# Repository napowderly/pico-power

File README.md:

# pico-power

Wooohooo a new package!

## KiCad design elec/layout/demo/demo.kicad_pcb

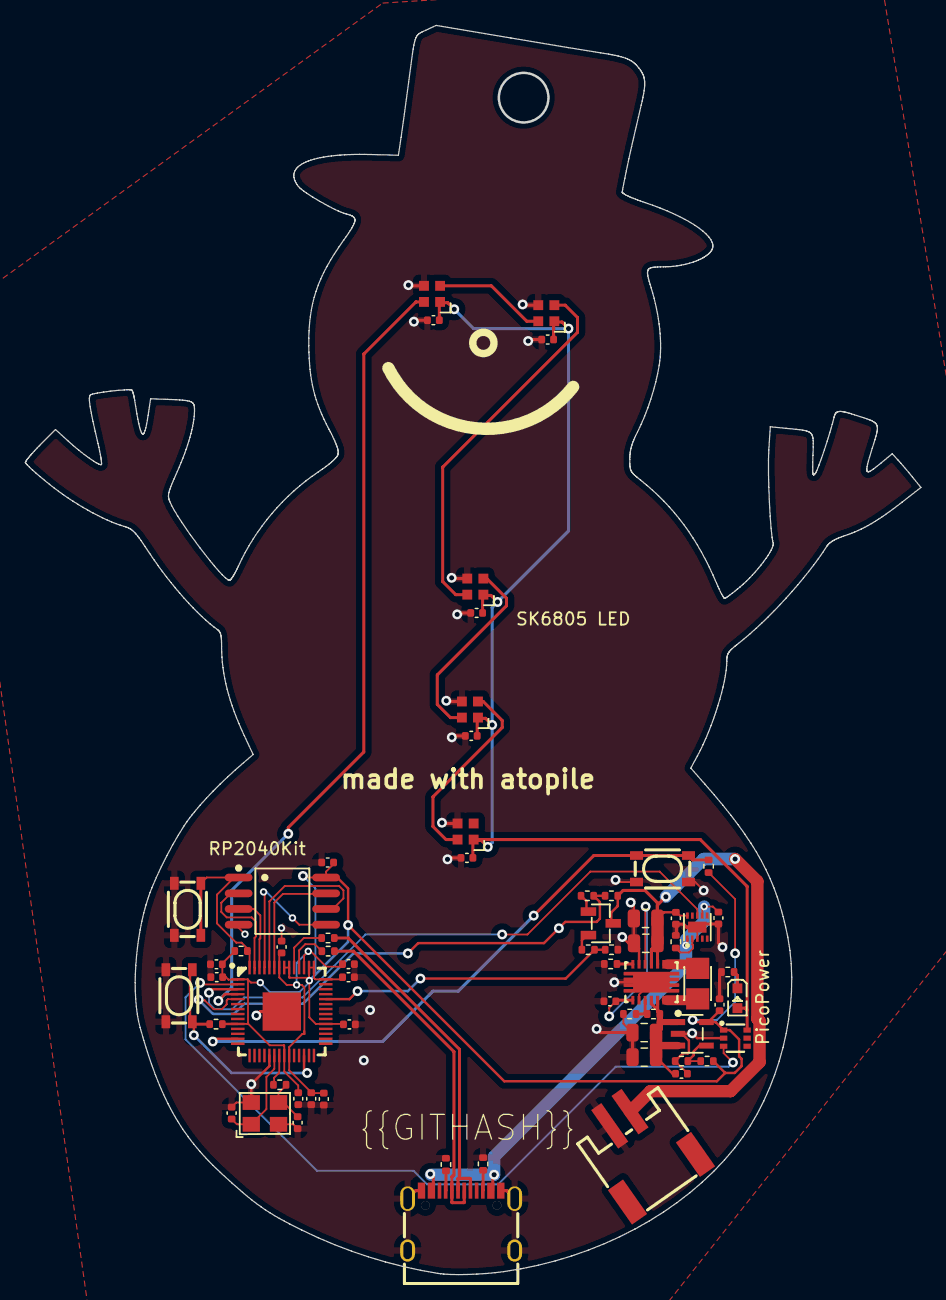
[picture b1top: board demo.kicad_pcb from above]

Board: 2 copper layers, 72.3 x 100.8 mm, 65 parts (0 on the bottom side), 43 nets.

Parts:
C1, C2, C3, C4: 25V 10uF X5R ±10% 0805 Multilayer Ceramic Capacit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; C0805
C5, C12, C13, C14, C15, C16, C18, C19, C20, C22, C23, C24, C25, C26: 16V 100nF X7R ±10% 0402 Multilayer Ceramic Capaci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; C0402
C6, C7, C8, C9, C17, C21: 25V 1uF X5R ±10% 0402 Multilayer Ceramic Capacito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; C0402
C10, C11: 50V 18pF C0G ±5% 0402 Multilayer Ceramic Capacito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; C0402
L1: IND-SMD_L2.5-W2.0_WPN252012H
LED1: LED0603-RD
Q1: SOT-23-3_L2.9-W1.3-P1.90-LS2.4-BR
R1: 62.5mW Thick Film Resistors 50V ±100ppm/℃ ±1% 107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; R0402
R2: 62.5mW Thick Film Resistors 50V ±100ppm/℃ ±5% 360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; R0402
R3: 62.5mW Thick Film Resistors 50V ±100ppm/℃ ±1% 100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; R0402
R4: 62.5mW Thick Film Resistors 50V ±1% ±200ppm/℃ 100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; R0402
R5: 62.5mW Thick Film Resistors 50V ±100ppm/℃ ±1% 24.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; R0402
R6: 62.5mW Thick Film Resistors 50V ±100ppm/℃ ±1% 4.0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; R0402
R7: 62.5mW Thick Film Resistors 50V ±100ppm/℃ ±1% 1MΩ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; R0402
R8: 62.5mW Thick Film Resistors ±100ppm/℃ ±1% 17.4kΩ 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; R0402
R9: 62.5mW Thick Film Resistors 50V ±100ppm/℃ ±1% 10.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; R0402
R10: 62.5mW Thick Film Resistors 75V ±1% ±100ppm/℃ 576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; R0402
R11, R12, R16: 62.5mW Thick Film Resistors 50V ±100ppm/℃ ±1% 10k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; R0402
R13: 62.5mW Thick Film Resistors 50V ±100ppm/℃ ±1% 1kΩ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; R0402
R14, R15: 62.5mW Thick Film Resistors 50V ±100ppm/℃ ±1% 27Ω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; R0402
R17, R18: 62.5mW Thick Film Resistors 50V ±100ppm/℃ ±1% 4.7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; R0402
R19: 62.5mW Thin Film Resistor 50V ±50ppm/℃ ±1% 309Ω 0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; R0402
U1: CONN-SMD_P2.00_S2B-PH-SM4-TB-LF-SN
U2: VSON-14_L4.0-W3.0-P0.50-BL-EP_TI_DSJ
U3: SOT-23-5_L3.0-W1.7-P0.95-LS2.8-BL
U4: SC-70-6_L2.2-W1.3-P0.65-LS2.1-BR
U5: WSON-10_L2.0-W2.0-P0.40-BL-EP
U6: LQFN-56_L7.0-W7.0-P0.4-EP
U7, U8, U11: KEY-SMD_4P-L4.2-W3.2-P2.20-LS4.6
U9: OSC-SMD_4P-L3.2-W2.5-BL
U10: SOIC-8_L5.3-W5.3-P1.27-LS8.0-BL
U12: USB-C-SMD_KH-TYPE-C-16P
U13, U14, U15, U16, U17: LED-SMD_4P-L2.0-W2.0-BR

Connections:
cathode: LED1.1, R19.1
cc1: R17.1, U12.A5
cc2: R18.1, U12.B5
dm: R15.1, U12.A7, U12.B7
dp: R14.2, U12.A6, U12.B6
io0: U6.53, U10.5
io1: U6.55, U10.2
io2: U6.54, U10.3
io3: U6.51, U10.7
iset: R10.1, U5.2
l1: L1.1, U2.8, U2.9
l2: L1.2, U2.6, U2.7
led1.ic-vcc: U13.2, U14.4
led2.ic-vcc: U14.2, U15.4
led3.ic-vcc: U15.2, U16.4
led4.ic-vcc: U16.2, U17.4
micro-cs-1: R12.2, U6.56, U8.1, U8.2, U10.1
micro-sck: R16.2, U6.13, U11.1, U11.2
micro-sck-1: U6.52, U10.6
micro.micro-vcc: C18.1, C19.1, C20.1, C21.1, U6.23, U6.45, U6.50
micro.micro-vcc-1: U6.4, U13.4
micro.osc.osc-out: C11.1, R13.2, U9.3
psu-gnd: C1.2, C2.2, C3.2, C4.2, C5.2, C6.2, C7.2, C8.2, C9.2, C10.2, C11.2, C12.2, C13.2, C14.2, C15.2, C16.2, C17.2, C18.2, C19.2, C20.2, C21.2, C22.2, C23.2, C24.2, C25.2, C26.2, R2.2, R6.2, R7.2, R9.2, R10.2, R17.2, R18.2, R19.2, U1.1, U2.2, U2.13, U2.15, U3.2, U4.2, U5.3, U5.11, U6.19, U6.57, U7.3, U7.4, U8.3, U8.4, U9.2, U9.4, U10.4, U11.3, U11.4, U12.1, U12.2, U12.3, U12.4, U12.A1, U12.A12, U12.B1, U12.B12, U13.3, U14.3, U15.3, U16.3, U17.3
psu-vcc: C7.1, C12.1, C13.1, C14.1, C15.1, C16.1, C17.1, R8.1, R11.1, R12.1, R16.1, U3.5, U4.1, U6.1, U6.10, U6.22, U6.33, U6.42, U6.43, U6.44, U6.48, U6.49, U10.8
psu-vcc-1: C22.1, C23.1, C24.1, C25.1, C26.1, LED1.2, U4.6, U13.1, U14.1, U15.1, U16.1, U17.1
psu-vcc-2: C8.1, U5.1, U5.7, U12.A4, U12.A9, U12.B4, U12.B9
psu-vcc-3: U4.3, U6.2
psu-vcc-4: R1.2, R2.1, U6.38
psu-vcc-5: R3.2, R4.1, U6.5
psu-vcc-6: U5.8, U6.3
psu.battery-vcc: C1.1, C2.1, C9.1, Q1.3, R3.1, U1.2, U2.10, U2.11, U5.10
psu.battery_vdiv.pfet-gnd: Q1.1, R4.2
psu.battery_vdiv.pfet-vcc: Q1.2, R1.1
psu.buck_boost-vcc: C3.1, C4.1, C6.1, R5.1, U2.4, U2.5, U3.1, U3.3
psu.buck_boost.feedback_div-out: R5.2, R6.1, U2.3
psu.buck_boost.ic-pg: R7.1, U2.14
psu.ldo.feedback_div-out: R8.2, R9.1, U3.4
run: R11.2, U6.26, U7.1, U7.2
usb_dm: R15.2, U6.46
usb_dp: R14.1, U6.47
vina: C5.1, U2.1, U2.12
xin: C10.1, U6.20, U9.1
xout: R13.1, U6.21

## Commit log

2024-04-17 Configure project
2024-04-18 demo board ready to build
2024-04-18 remove designators from silk
2024-04-18 adding files
